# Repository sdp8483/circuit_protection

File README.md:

https://samueldperry.com/2025/02/15/circuit-protection-with-discrete-components/

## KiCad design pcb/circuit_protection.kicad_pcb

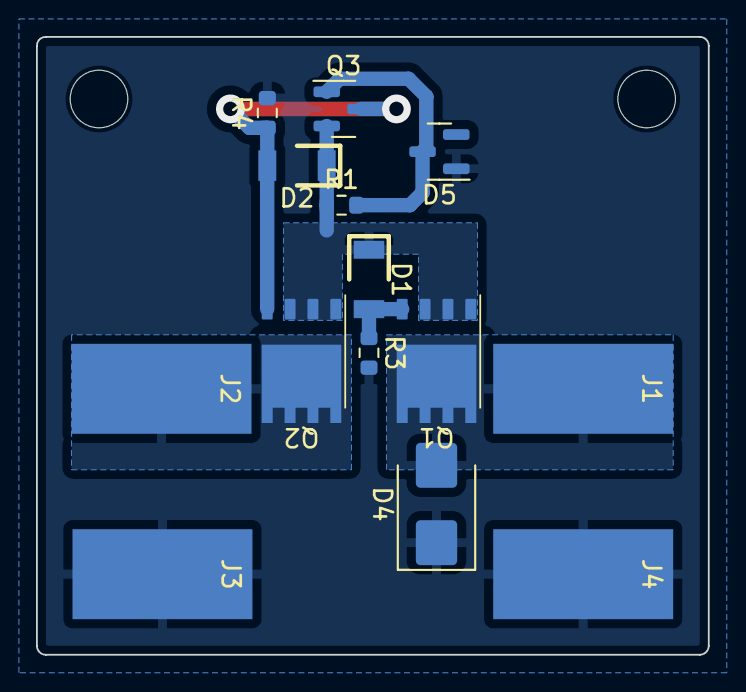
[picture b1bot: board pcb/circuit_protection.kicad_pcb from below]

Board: 2 copper layers, 37.3 x 34.3 mm, 14 parts (14 on the bottom side), 7 nets.

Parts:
D1, D2: 15V; Nexperia_BZV55_SOD80C
D4: SMBJ45CA; D_SMB
D5: 43V; SOT-23
J1, J2, J3, J4: Conn_01x01; SolderWirePad_1x01_SMD_5x10mm
Q1, Q2: G65P06D5
Q3: MMBT2907A; SOT-23
R1, R3, R4: 10k; R_0603_1608Metric

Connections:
/Vin: D4.2 (A2), J1.1, Q1.5 (D)
/Vout: J2.1, Q2.5 (D)
GND: D4.1 (A1), D5.1 (A), J3.1, J4.1, R3.2, R4.2
unnamed: D1.2 (A), Q1.4 (G), R3.1
unnamed: D1.1 (K), D2.1 (K), Q1.1 (S), Q1.2 (S), Q1.3 (S), Q2.1 (S), Q2.2 (S), Q2.3 (S), Q3.2 (E), R1.1
unnamed: D2.2 (A), Q2.4 (G), Q3.3 (C), R4.1
unnamed: D5.3 (K), Q3.1 (B), R1.2

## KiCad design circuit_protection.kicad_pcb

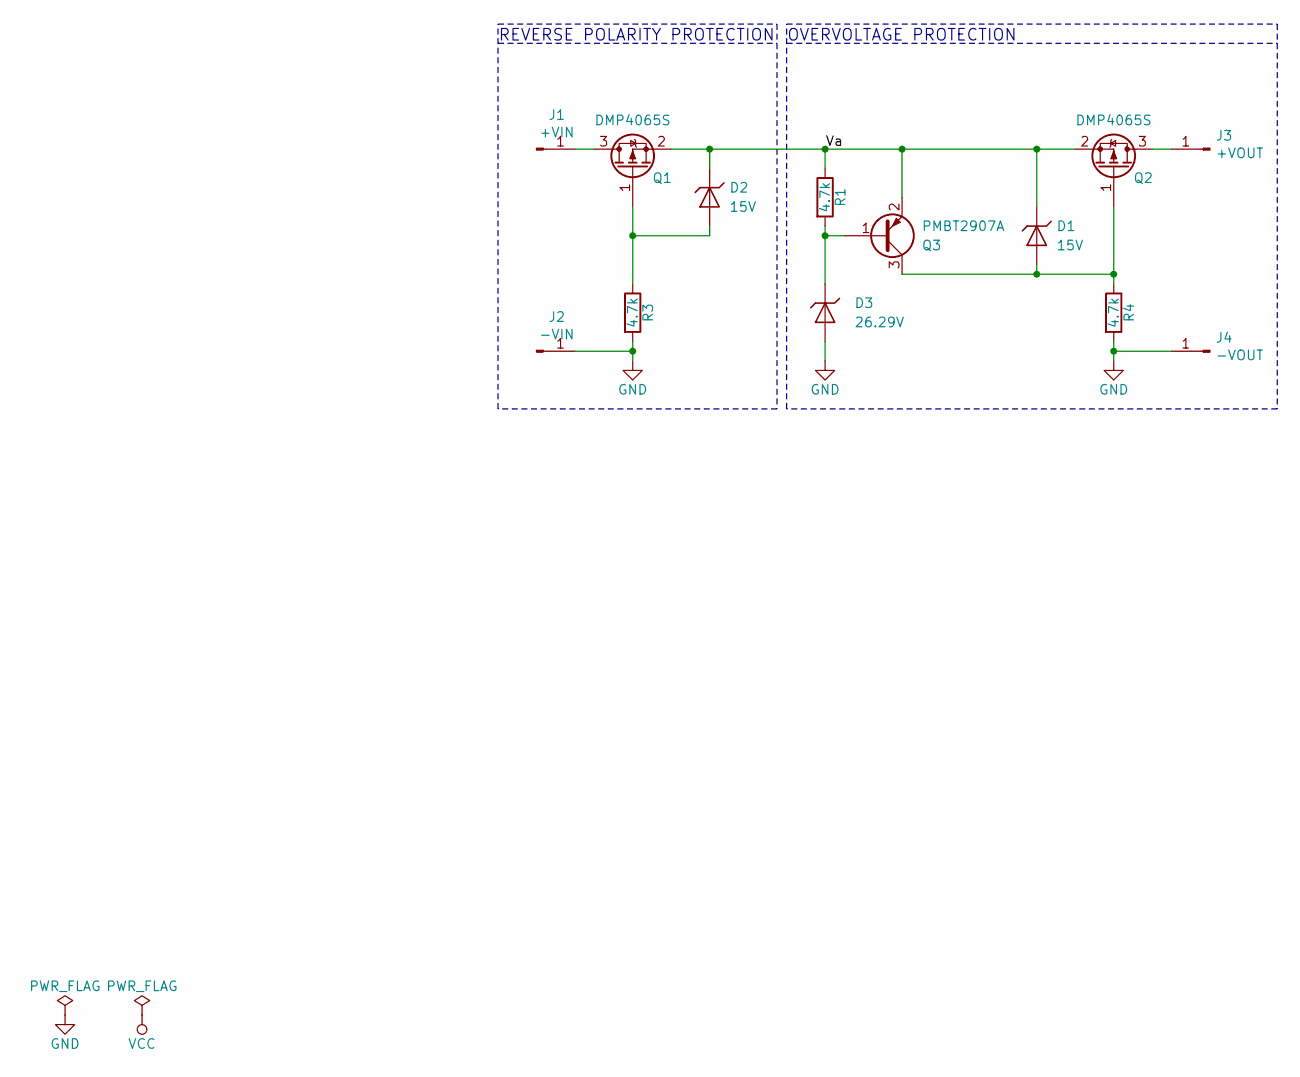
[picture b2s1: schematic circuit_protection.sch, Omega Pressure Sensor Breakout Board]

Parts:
D1, D2: 15V; Vishay_TZM5258B_SOD80; Mfg Part Number TLZ15A-GS08
D3: 26.29V; D_SOD-323F; Mfg Part Number DDZ27CSF-7
J1: +VIN; TestPoint_THTPad_D1.5mm_Drill0.7mm
J2: -VIN; TestPoint_THTPad_D1.5mm_Drill0.7mm
J3: +VOUT; TestPoint_THTPad_D1.5mm_Drill0.7mm
J4: -VOUT; TestPoint_THTPad_D1.5mm_Drill0.7mm
Q1, Q2: DMP4065S; SOT-23; Mfg Part Number DMP4065S
Q3: PMBT2907A; SOT-23; Mfg Part Number PMBT2907A,235
R1, R3, R4: 4.7k; R_Axial_DIN0207_L6.3mm_D2.5mm_P10.16mm_Horizontal

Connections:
/Va: D1.1 (K), D2.1 (K), Q1.2 (S), Q2.2 (S), Q3.2 (E), R1.1
GND: D3.2 (A), J2.1, J4.1, R3.2, R4.2
unnamed: D1.2 (A), Q2.1 (G), Q3.3 (C), R4.1
unnamed: D2.2 (A), Q1.1 (G), R3.1
unnamed: D3.1 (K), Q3.1 (B), R1.2
unnamed: J1.1, Q1.3 (D)
unnamed: J3.1, Q2.3 (D)

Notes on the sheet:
OVERVOLTAGE PROTECTION
REVERSE POLARITY PROTECTION

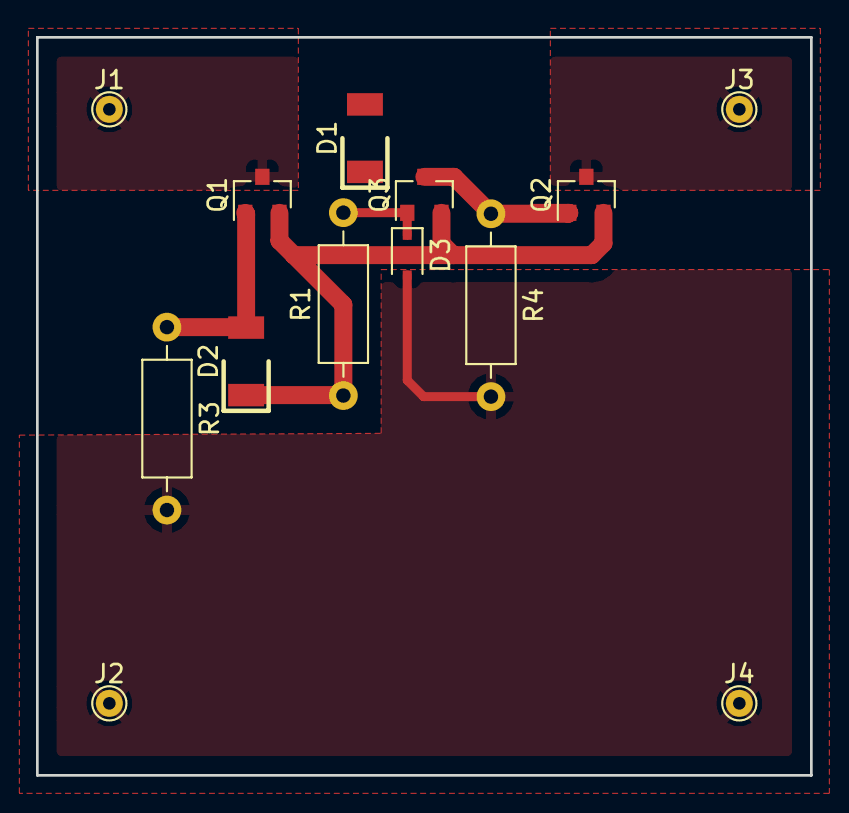
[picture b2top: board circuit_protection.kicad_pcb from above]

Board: 2 copper layers, 43.0 x 41.0 mm, 13 parts (0 on the bottom side), 7 nets.

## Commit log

2018-12-23 init commit
2018-12-29 ignore *.DS_Store
2018-12-29 circuit analysis start
2018-12-30 start schematic
2018-12-31 at home etch board layout
2018-12-31 label node A on schematic
2018-12-31 ignore temp xlsx files
2018-12-31 add zener to limit gate voltage of Q2
2018-12-31 annotate new zener
2018-12-31 place new zener, not connected
2019-01-01 data from circuit containing zener for Q2
2019-01-01 remove Va measurments for 10V tab
2019-01-01 charts, pictures, and mistakes
2019-01-01 measured Q2 temp at 30Vin
2019-01-01 started working on error calulations
2019-01-06 remove python code, sticking to easy excel
2023-04-18 new branch init commit
2023-04-18 add 3d models
2023-04-18 add footprints
2023-04-18 add symbol
2023-04-18 set Vin/Vout footprint
2023-04-18 Create fp-lib-table
2023-04-18 remove LED
2023-04-18 plot gerbers
2023-04-18 create gcode
2023-04-18 remove inner mill
